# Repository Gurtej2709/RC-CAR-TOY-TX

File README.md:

# RC-CAR-TOY-TX
Custom PCB design for a toy RC car, featuring dedicated transmitter (TX) and receiver (RX) circuits for wireless

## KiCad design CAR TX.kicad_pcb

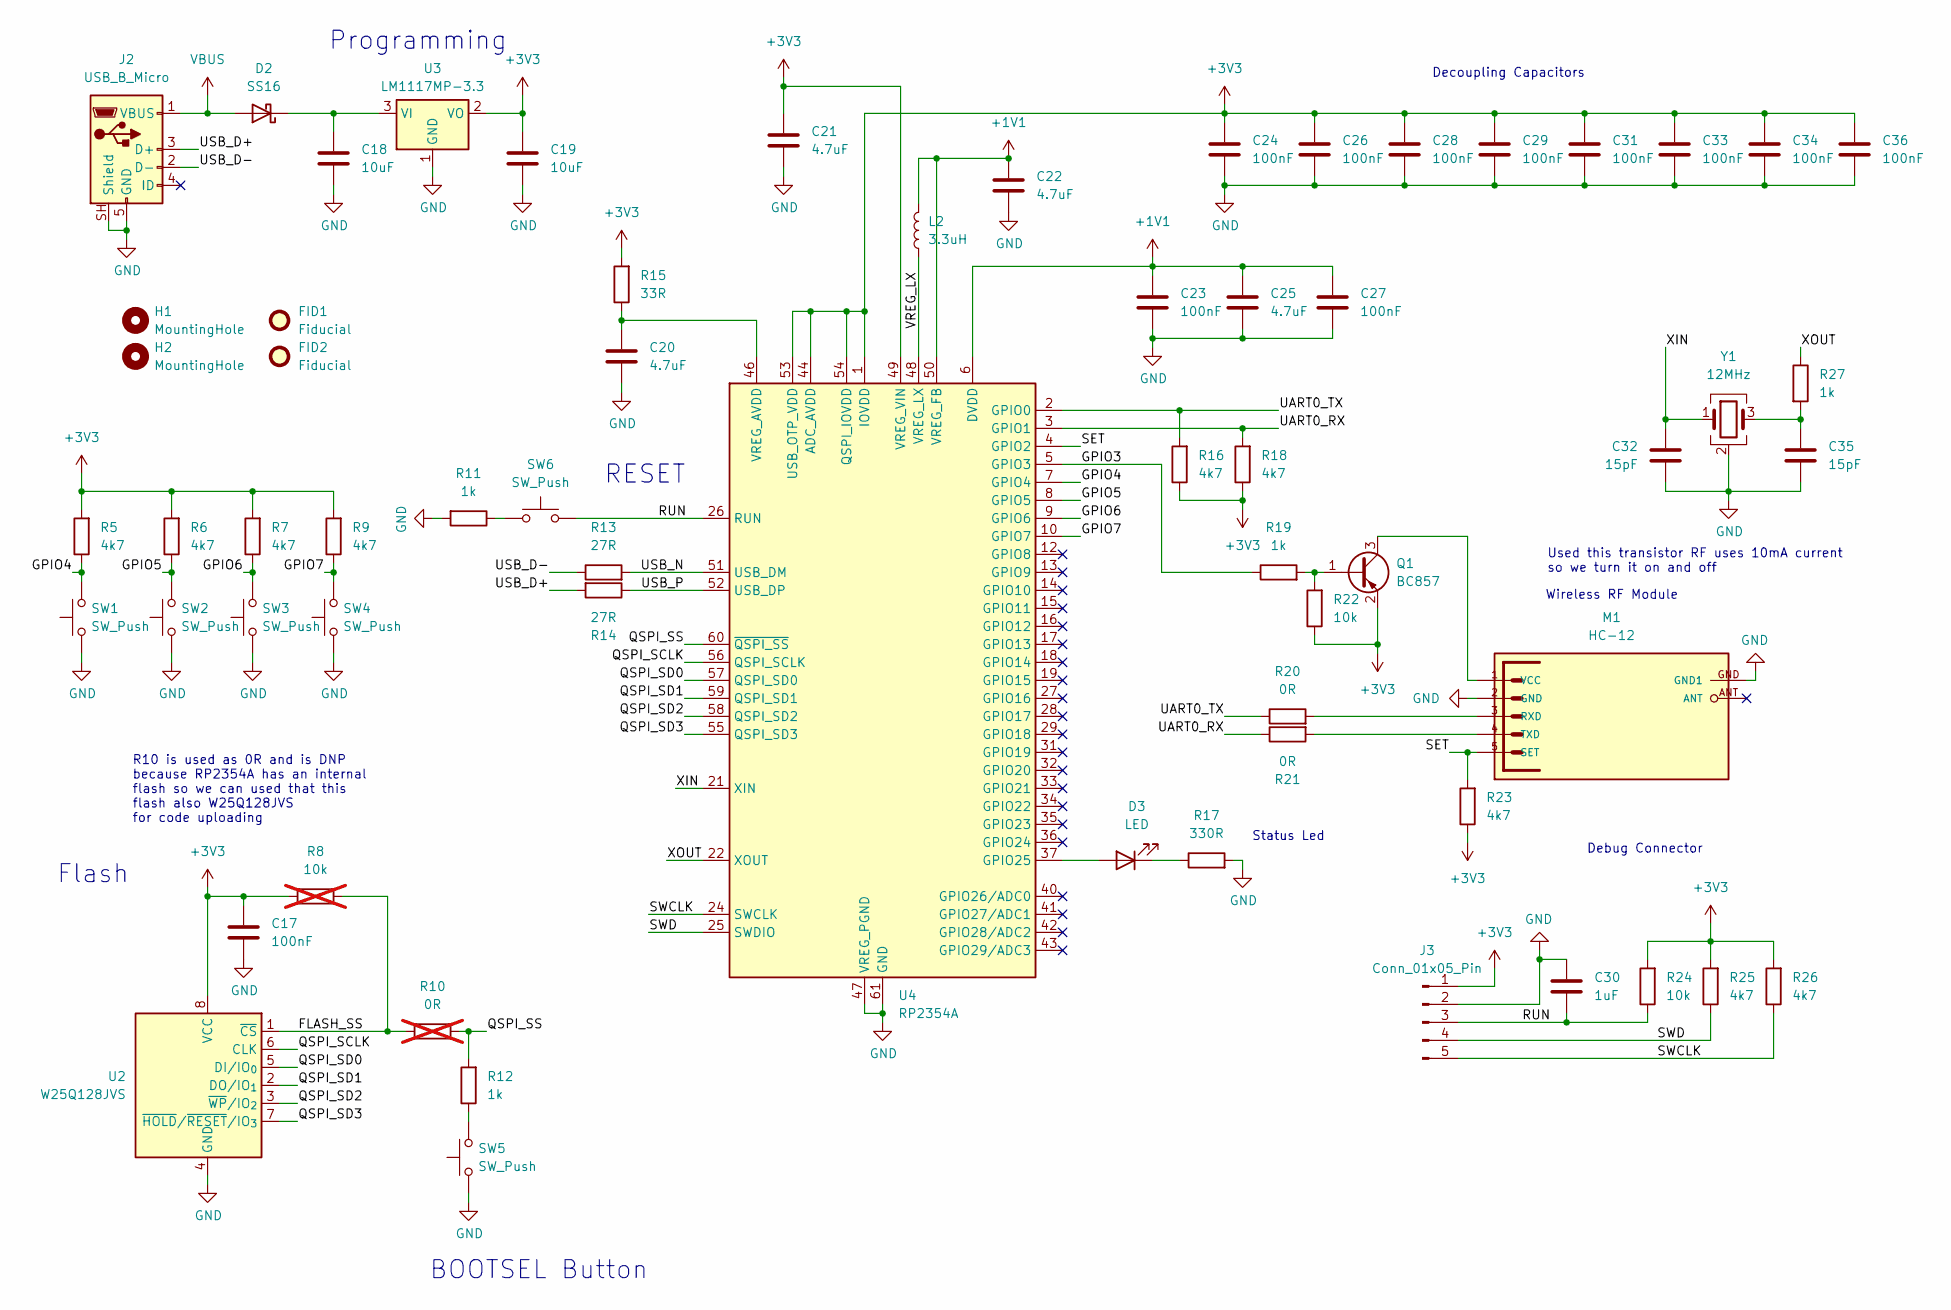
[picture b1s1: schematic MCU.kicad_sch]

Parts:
C17, C23, C24, C26, C27, C28, C29, C31, C33, C34, C36: 100nF; C_0603_1608Metric_Pad1.08x0.95mm_HandSolder
C18, C19: 10uF; C_1206_3216Metric_Pad1.33x1.80mm_HandSolder
C20, C21, C22, C25: 4.7uF; C_0603_1608Metric_Pad1.08x0.95mm_HandSolder
C30: 1uF; C_0603_1608Metric_Pad1.08x0.95mm_HandSolder
C32, C35: 15pF; C_0603_1608Metric_Pad1.08x0.95mm_HandSolder
D2: SS16; D_SMA
D3: LED; LED_0603_1608Metric_Pad1.05x0.95mm_HandSolder
FID1, FID2: Fiducial; Fiducial_1.5mm_Mask3mm
H1, H2: MountingHole; MountingHole_3.2mm_M3_DIN965_Pad
J2: USB_B_Micro; USB_Micro-B_Amphenol_10103594-0001LF_Horizontal
J3: Conn_01x05_Pin; PinHeader_1x05_P2.54mm_Vertical
L2: 3.3uH; L_1008_2520Metric_Pad1.43x2.20mm_HandSolder
M1: HC-12
Q1: BC857; SOT-23
R5, R6, R7, R9, R16, R18, R23, R25, R26: 4k7; R_0603_1608Metric_Pad0.98x0.95mm_HandSolder
R8: 10k; R_0603_1608Metric_Pad0.98x0.95mm_HandSolder; not fitted
R10: 0R; R_0603_1608Metric_Pad0.98x0.95mm_HandSolder; not fitted
R11, R12, R19, R27: 1k; R_0603_1608Metric_Pad0.98x0.95mm_HandSolder
R13, R14: 27R; R_0603_1608Metric_Pad0.98x0.95mm_HandSolder
R15: 33R; R_0603_1608Metric_Pad0.98x0.95mm_HandSolder
R17: 330R; R_0603_1608Metric_Pad0.98x0.95mm_HandSolder
R20, R21: 0R; R_0603_1608Metric_Pad0.98x0.95mm_HandSolder
R22, R24: 10k; R_0603_1608Metric_Pad0.98x0.95mm_HandSolder
SW1, SW2, SW3, SW4, SW5, SW6: SW_Push; SW_SPST_B3SL-1022P
U2: W25Q128JVS; SOIC-8_5.3x5.3mm_P1.27mm
U3: LM1117MP-3.3; SOT-223-3_TabPin2
U4: RP2354A; QFN-60-1EP_7x7mm_P0.4mm_EP3.4x3.4mm_ThermalVias
Y1: 12MHz; Crystal_SMD_SeikoEpson_FA238-4Pin_3.2x2.5mm

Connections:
+1V1: C22.1, C23.1, C25.1, C27.1, L2.2, U4.6 (DVDD), U4.23 (DVDD), U4.39 (DVDD), U4.50 (VREG_FB)
+3V3: C17.1, C19.1, C21.1, C24.1, C26.1, C28.1, C29.1, C31.1, C33.1, C34.1, C36.1, J3.1, Q1.2 (E), R5.2, R6.2, R7.2, R8.1, R9.2, R15.2, R16.1, R18.1, R22.1, R23.1, R24.2, R25.2, R26.2, U2.8 (VCC), U3.2 (VO), U4.1 (IOVDD), U4.11 (IOVDD), U4.20 (IOVDD), U4.30 (IOVDD), U4.38 (IOVDD), U4.44 (ADC_AVDD), U4.45 (IOVDD), U4.49 (VREG_VIN), U4.53 (USB_OTP_VDD), U4.54 (QSPI_IOVDD); also elsewhere on the board
/MCU/FLASH_SS: R8.2, R10.1, U2.1 (~CS)
/MCU/GPIO3: R19.1, U4.5 (GPIO3)
/MCU/GPIO4: R5.1, SW1.2, U4.7 (GPIO4)
/MCU/GPIO5: R6.1, SW2.2, U4.8 (GPIO5)
/MCU/GPIO6: R7.1, SW3.2, U4.9 (GPIO6)
/MCU/GPIO7: R9.1, SW4.2, U4.10 (GPIO7)
/MCU/QSPI_SCLK: U2.6 (CLK), U4.56 (QSPI_SCLK)
/MCU/QSPI_SD0: U2.5 (DI/IO_{0}), U4.57 (QSPI_SD0)
/MCU/QSPI_SD1: U2.2 (DO/IO_{1}), U4.59 (QSPI_SD1)
/MCU/QSPI_SD2: U2.3 (~WP/IO_{2}), U4.58 (QSPI_SD2)
/MCU/QSPI_SD3: U2.7 (~HOLD/~RESET/IO_{3}), U4.55 (QSPI_SD3)
/MCU/QSPI_SS: R10.2, R12.2, U4.60 (~QSPI_SS)
/MCU/RUN: C30.2, J3.3, R24.1, SW6.2, U4.26 (RUN)
/MCU/SET: M1.5 (SET), R23.2, U4.4 (GPIO2)
/MCU/SWCLK: J3.5, R26.1, U4.24 (SWCLK)
/MCU/SWD: J3.4, R25.1, U4.25 (SWDIO)
/MCU/UART0_RX: R18.2, R21.1, U4.3 (GPIO1)
/MCU/UART0_TX: R16.2, R20.1, U4.2 (GPIO0)
/MCU/USB_D+: J2.3 (D+), R14.2
/MCU/USB_D-: J2.2 (D-), R13.1
/MCU/USB_N: R13.2, U4.51 (USB_DM)
/MCU/USB_P: R14.1, U4.52 (USB_DP)
/MCU/VREG_LX: L2.1, U4.48 (VREG_LX)
/MCU/XIN: C32.1, U4.21 (XIN), Y1.1
/MCU/XOUT: R27.1, U4.22 (XOUT)
GND: C17.2, C18.2, C19.2, C20.2, C21.2, C22.2, C23.2, C24.2, C25.2, C26.2, C27.2, C28.2, C29.2, C30.1, C31.2, C32.2, C33.2, C34.2, C35.2, C36.2, J2.5 (GND), J2.SH (Shield), J3.2, M1.2 (GND), M1.GND (GND1), M1.GND1, R11.2, R17.2, SW1.1, SW2.1, SW3.1, SW4.1, SW5.1, U2.4 (GND), U3.1 (GND), U4.47 (VREG_PGND), U4.61 (GND), Y1.2 (G), Y1.4 (G); also elsewhere on the board
unnamed: C35.1, R27.2, Y1.3
unnamed: C18.1, D2.1 (K), U3.3 (VI)
unnamed: D3.2 (A), U4.37 (GPIO25)
unnamed: D3.1 (K), R17.1
unnamed: M1.3 (RXD), R20.2
unnamed: M1.4 (TXD), R21.2
unnamed: M1.1 (VCC), Q1.3 (C)
unnamed: Q1.1 (B), R19.2, R22.2
unnamed: R11.1, SW6.1
unnamed: R12.1, SW5.2
unnamed: C20.1, R15.1, U4.46 (VREG_AVDD)
VBUS: D2.2 (A), J2.1 (VBUS)

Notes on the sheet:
Status Led
Programming
Wireless RF Module
Decoupling Capacitors
R10 is used as 0R and is DNP because RP2354A has an internal flash so we can used that this flash also W25Q128JVS for code uploading
RESET
Used this transistor RF uses 10mA current so we turn it on and off
Debug Connector
Flash
BOOTSEL Button

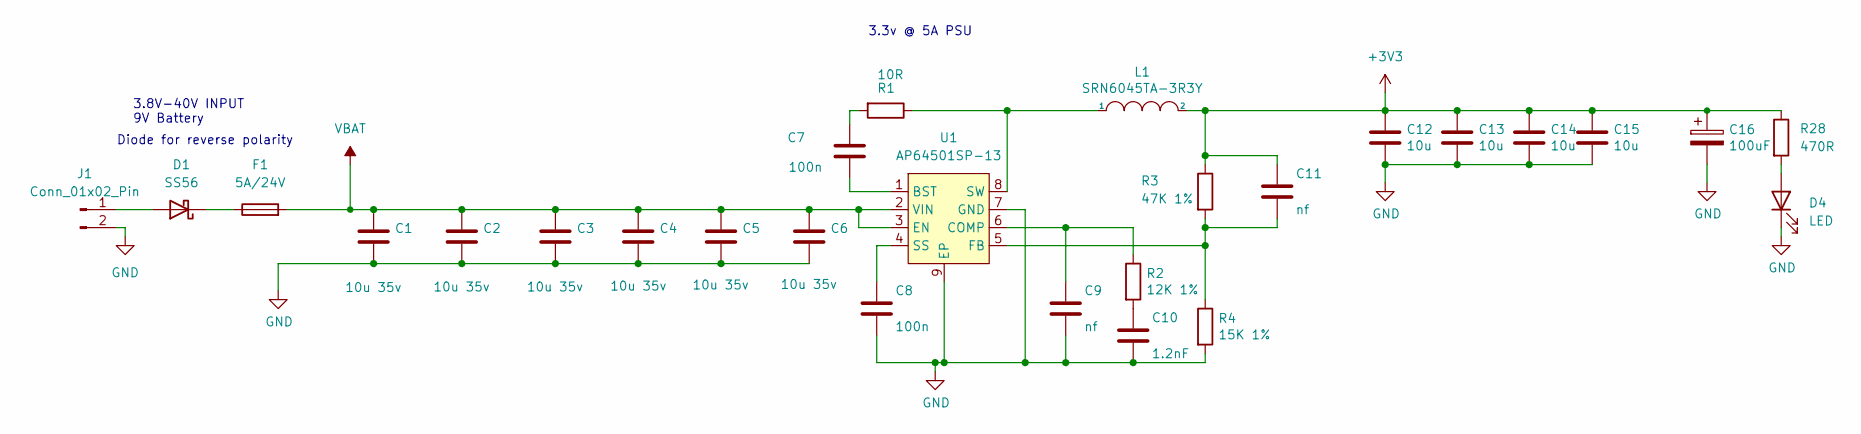
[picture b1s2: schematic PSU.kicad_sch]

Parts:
C1, C2, C3, C4, C5, C6: 10u 35v; C_0805_2012Metric; Part Description 10uF 10% or 20% 35V Ceramic Capacitor X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
C7, C8: 100n; C_0402_1005Metric; Part Description 0.1uF 10% 16V Ceramic Capacitor X7R 040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
C9: nf; C_0402_1005Metric
C10: 1.2nF; C_0402_1005Metric; Part Description 1200pF 10% 10V Ceramic Capacitor X5R 04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
C11: nf; C_0402_1005Metric; Part Description 27pF 5% 50V Ceramic Capacitor C0G, NP0 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
C12, C13, C14, C15: 10u; C_0805_2012Metric; Part Description 10uF 10% 10V Ceramic Capacitor X7R 0805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
C16: 100uF; CP_EIA-7343-31_Kemet-D; Part Description Capacitor, SP-Cap, 100u, 6.3V, 15mR ESR
D1: SS56; D_SMC
D4: LED; LED_0603_1608Metric_Pad1.05x0.95mm_HandSolder
F1: 5A/24V; Fuse_2512_6332Metric_Pad1.52x3.35mm_HandSolder
J1: Conn_01x02_Pin; PinHeader_1x02_P2.54mm_Vertical
L1: SRN6045TA-3R3Y; L_Bourns_SRN6045TA; Part Description 3.3µH Semi-Shielded Wirewound Inductor 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
R1: 10R; R_0402_1005Metric; Part Description Resistor 10R M1005 1% 63mW
R2: 12K 1%; R_0402_1005Metric; Part Description Resistor 12K M1005 1% 63mW
R3: 47K 1%; R_0402_1005Metric; Part Description Resistor 47K M1005 1% 63mW
R4: 15K 1%; R_0402_1005Metric; Part Description Resistor 15K M1005 1% 63mW
R28: 470R; R_0603_1608Metric_Pad0.98x0.95mm_HandSolder
U1: AP64501SP-13; SOIC-8-1EP_3.9x4.9mm_P1.27mm_EP2.95x4.9mm_Mask2.71x3.4mm_Th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

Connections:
+3V3: C11.1, C12.1, C13.1, C14.1, C15.1, C16.1, L1.2, R3.1, R28.1; also elsewhere on the board
GND: C1.2, C2.2, C3.2, C4.2, C5.2, C6.2, C8.2, C9.2, C10.2, C12.2, C13.2, C14.2, C15.2, C16.2, D4.1 (K), J1.2, R4.2, U1.7 (GND), U1.9 (EP); also elsewhere on the board
unnamed: C7.1, R1.2
unnamed: C10.1, R2.2
unnamed: D1.2 (A), J1.1
unnamed: D1.1 (K), F1.1
unnamed: D4.2 (A), R28.2
unnamed: C7.2, U1.1 (BST)
unnamed: C9.1, R2.1, U1.6 (COMP)
unnamed: C11.2, R3.2, R4.1, U1.5 (FB)
unnamed: C8.1, U1.4 (SS)
unnamed: L1.1, R1.1, U1.8 (SW)
VBAT: C1.1, C2.1, C3.1, C4.1, C5.1, C6.1, F1.2, U1.2 (VIN), U1.3 (EN)

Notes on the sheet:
3.8V-40V INPUT 9V Battery
Diode for reverse polarity
3.3v @ 5A PSU

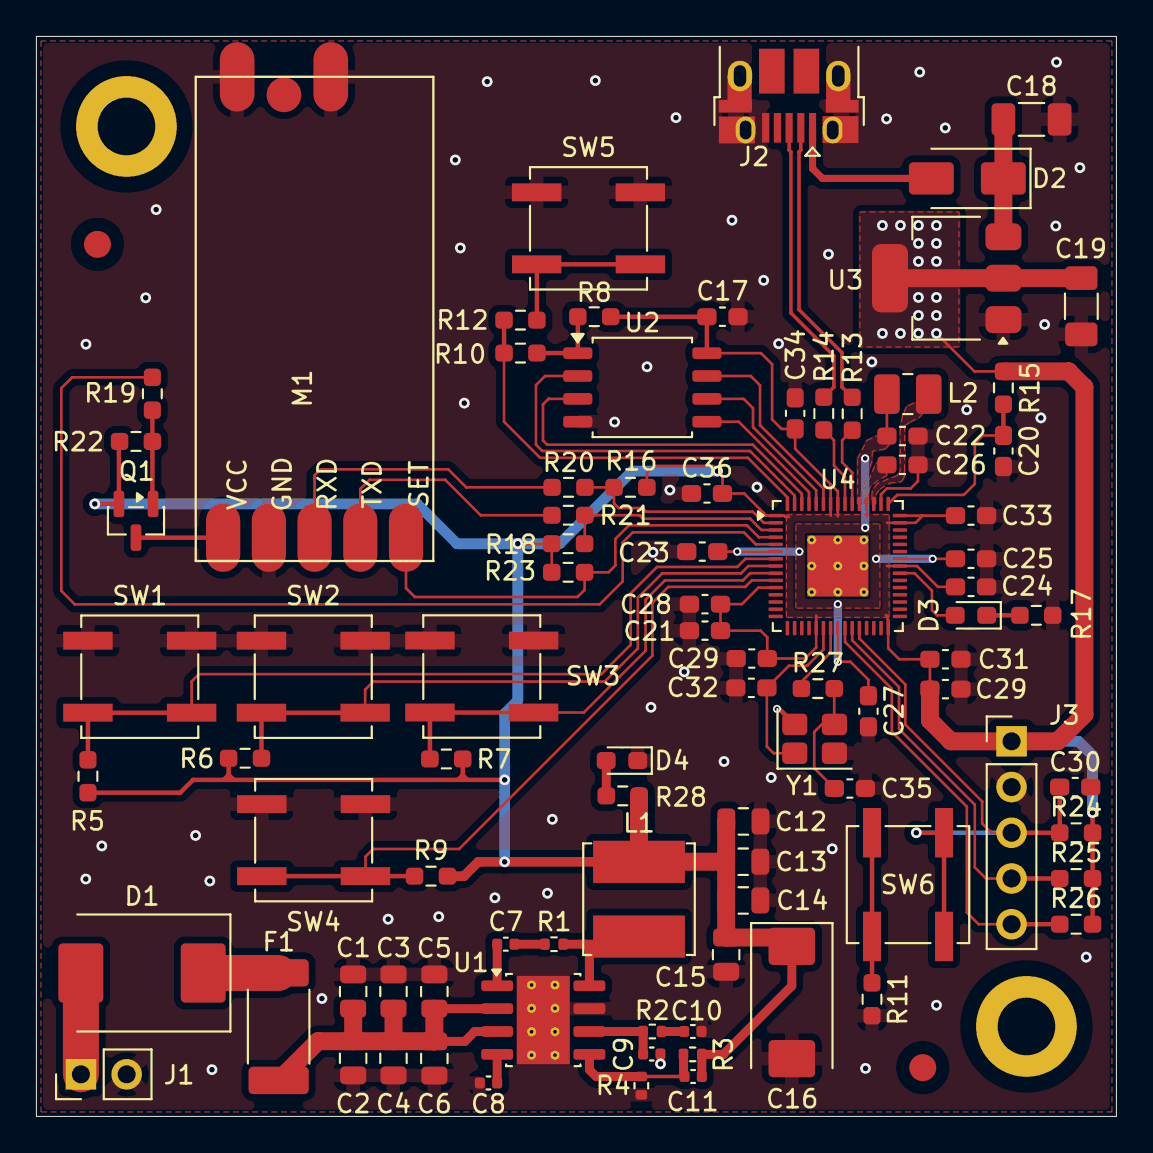
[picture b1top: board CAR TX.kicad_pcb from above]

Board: 2 copper layers, 60.0 x 60.0 mm, 92 parts (0 on the bottom side), 51 nets.

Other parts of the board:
C29#2: 100nF; C_0603_1608Metric_Pad1.08x0.95mm_HandSolder

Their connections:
+3V3: C29#2.1; also elsewhere on the board
GND: C29#2.2; also elsewhere on the board
